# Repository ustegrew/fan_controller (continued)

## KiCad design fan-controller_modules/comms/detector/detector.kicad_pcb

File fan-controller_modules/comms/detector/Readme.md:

# Eval: Detector

KiCad project for an evaluation board providing a fast detector for an AC signal >= 15kHz. This eval board will be realized on a protoype matrix board (pitch 2.54 mm).

Carrier sensitivity can be adjusted.

Detector provides an open collector output. Output is driven low (0V with respect to GND) when no carrier signal is being detected.

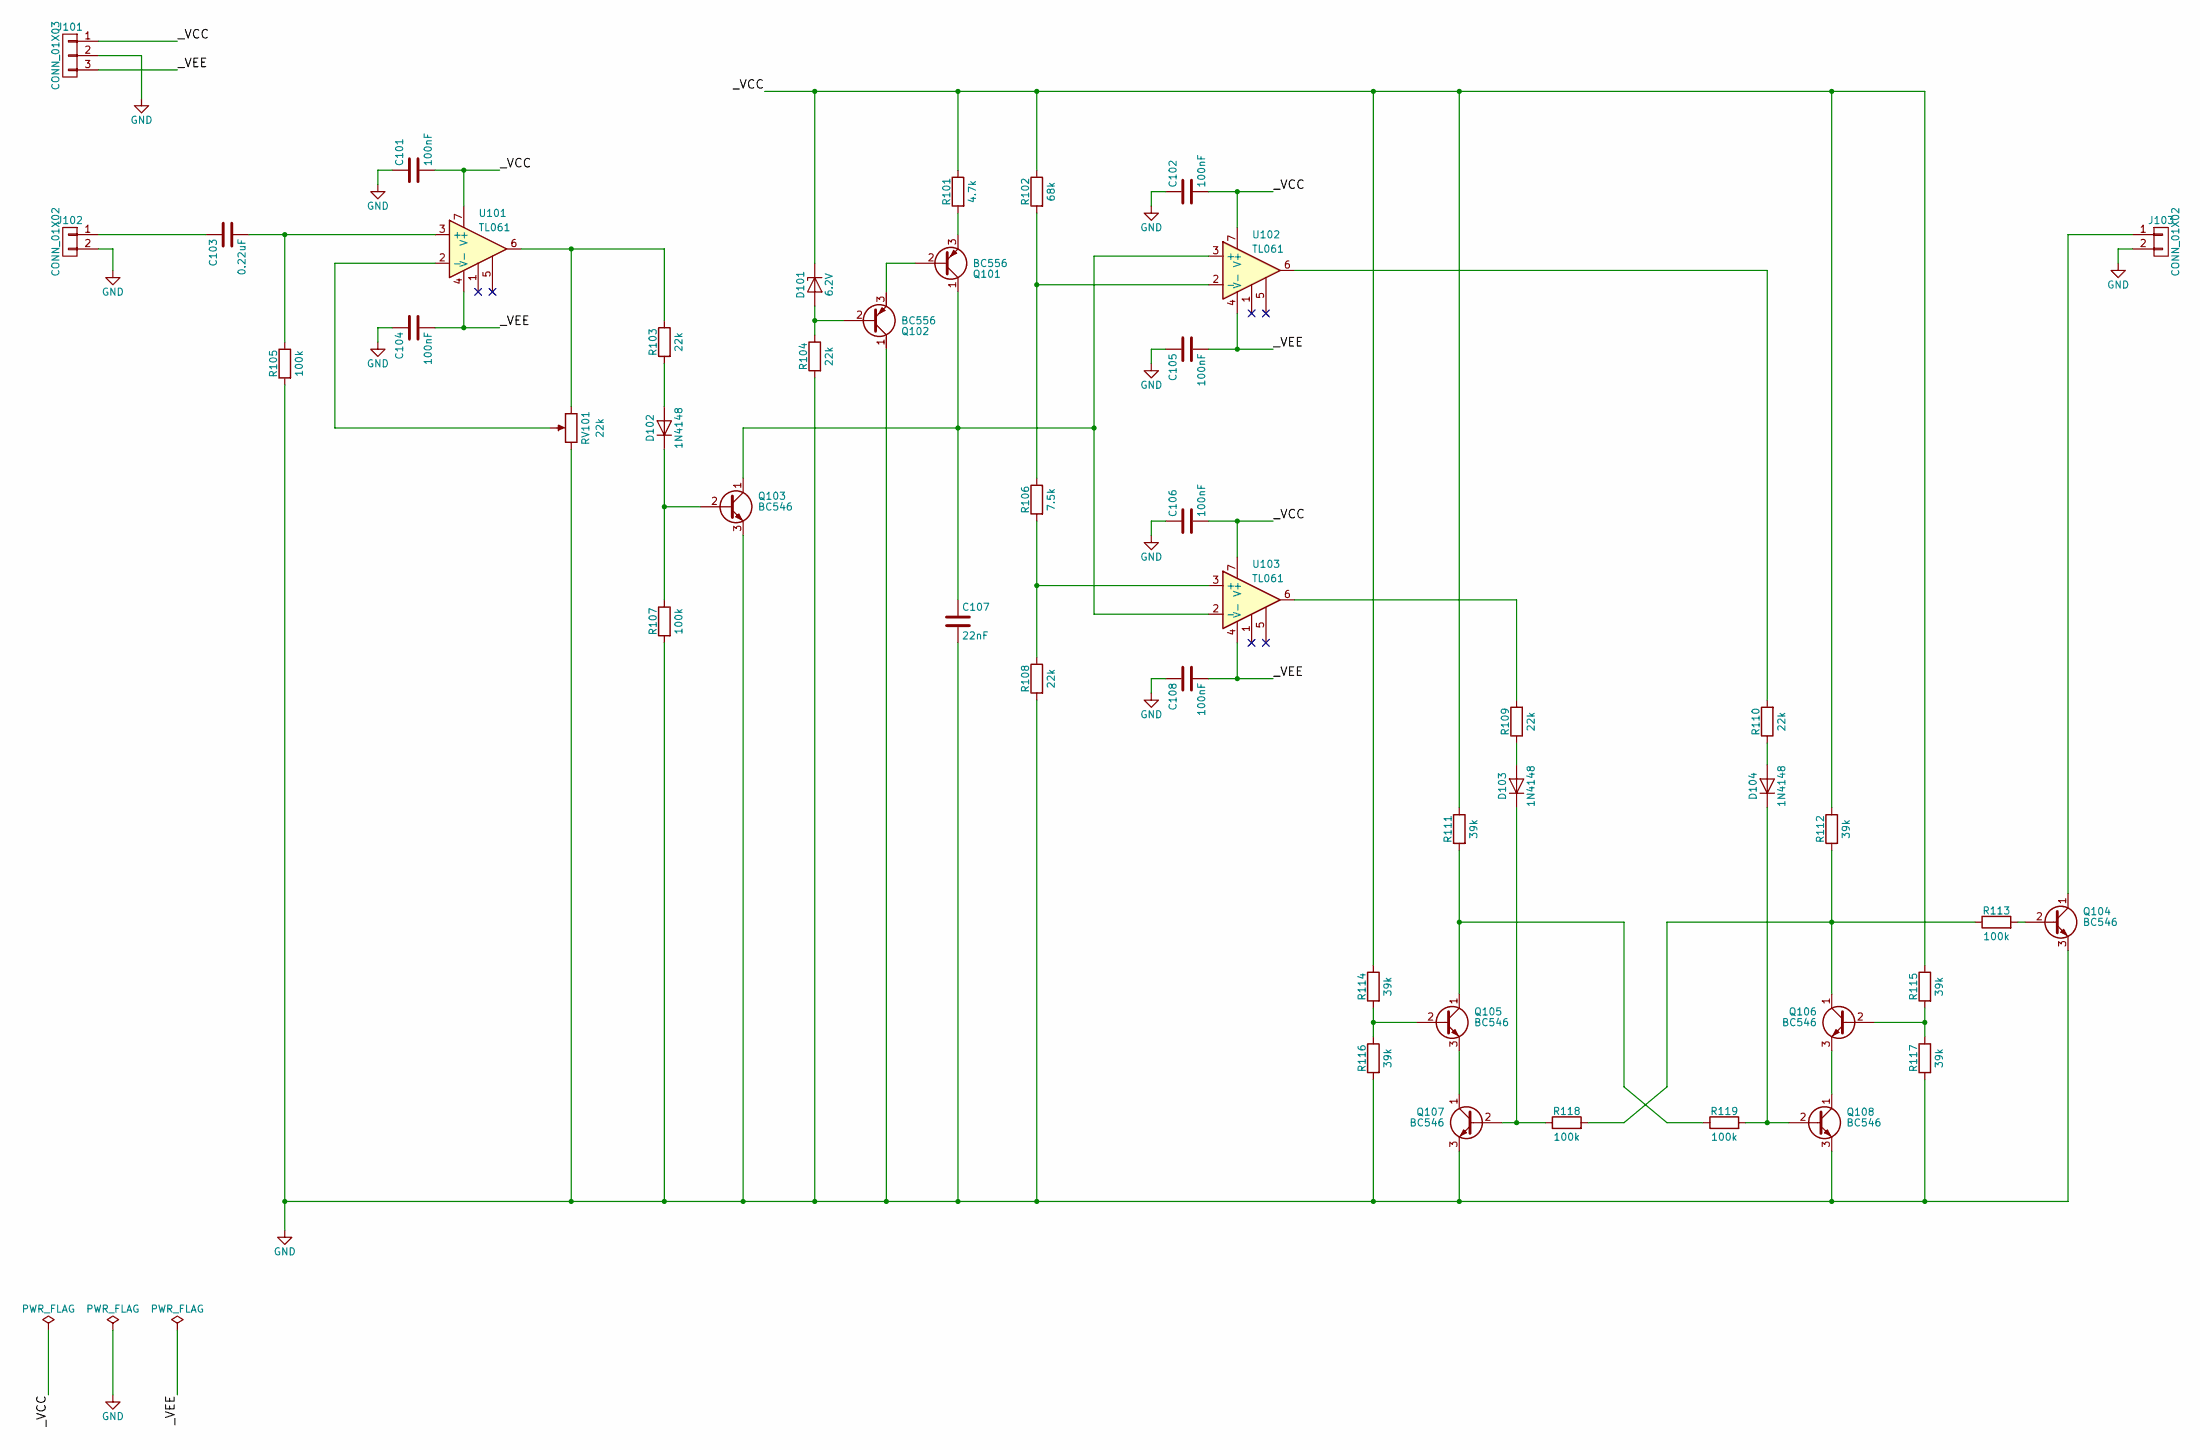
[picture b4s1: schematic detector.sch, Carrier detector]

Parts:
C101, C102: 100nF; C_Rect_L11.0mm_W4.3mm_P10.00mm_MKT
C103: 0.22uF; C_Rect_L7.0mm_W6.0mm_P5.00mm
C104, C105, C106, C108: 100nF; C_Rect_L13.0mm_W6.0mm_P10.00mm_FKS3_FKP3_MKS4
C107: 22nF; C_Rect_L7.2mm_W2.5mm_P5.00mm_FKS2_FKP2_MKS2_MKP2
D101: 6.2V; D_DO-35_SOD27_P7.62mm_Horizontal
D102, D103, D104: 1N4148; D_DO-35_SOD27_P7.62mm_Horizontal
J101: CONN_01X03; Pin_Header_Straight_1x03_Pitch2.54mm
J102, J103: CONN_01X02; Pin_Header_Straight_1x02_Pitch2.54mm
Q101, Q102: BC556; TO-92_Inline_Wide
Q103, Q104, Q105, Q106, Q107, Q108: BC546; TO-92_Inline_Wide
R101: 4.7k; R_Axial_DIN0207_L6.3mm_D2.5mm_P10.16mm_Horizontal
R102: 68k; R_Axial_DIN0414_L11.9mm_D4.5mm_P20.32mm_Horizontal
R103, R104, R108, R109, R110: 22k; R_Axial_DIN0207_L6.3mm_D2.5mm_P10.16mm_Horizontal
R105, R107, R113, R118, R119: 100k; R_Axial_DIN0207_L6.3mm_D2.5mm_P10.16mm_Horizontal
R106: 7.5k; R_Axial_DIN0414_L11.9mm_D4.5mm_P20.32mm_Horizontal
R111, R112, R114, R115, R116, R117: 39k; R_Axial_DIN0411_L9.9mm_D3.6mm_P15.24mm_Horizontal
RV101: 22k; Potentiometer_Trimmer_Piher_PT-10h3.8_Vertical_Px3.8mm_Py5.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
U101, U102, U103: TL061; DIP-8_W7.62mm_LongPads

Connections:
/_VCC: C101.2, C102.2, C106.2, D101.1 (K), J101.1, R101.1, R102.1, R111.1, R112.1, R114.1, R115.1, U101.7 (V+), U102.7 (V+), U103.7 (V+)
/_VEE: C104.2, C105.2, C108.2, J101.3, U101.4 (V-), U102.4 (V-), U103.4 (V-)
GND: C101.1, C102.1, C104.1, C105.1, C106.1, C107.2, C108.1, J101.2, J102.2, J103.2, Q102.1 (C), Q103.3 (E), Q104.3 (E), Q107.3 (E), Q108.3 (E), R104.2, R105.2, R107.2, R108.2, R116.2, R117.2, RV101.3
unnamed: C103.1, J102.1
unnamed: C103.2, R105.1, U101.3 (+)
unnamed: C107.1, Q101.1 (C), Q103.1 (C), U102.3 (+), U103.2 (-)
unnamed: D101.2 (A), Q102.2 (B), R104.1
unnamed: D102.1 (K), Q103.2 (B), R107.1
unnamed: D102.2 (A), R103.2
unnamed: D103.1 (K), Q107.2 (B), R118.1
unnamed: D103.2 (A), R109.1
unnamed: D104.1 (K), Q108.2 (B), R119.2
unnamed: D104.2 (A), R110.1
unnamed: J103.1, Q104.1 (C)
unnamed: Q101.2 (B), Q102.3 (E)
unnamed: Q101.3 (E), R101.2
unnamed: Q104.2 (B), R113.2
unnamed: Q105.1 (C), R111.2, R119.1
unnamed: Q105.2 (B), R114.2, R116.1
unnamed: Q105.3 (E), Q107.1 (C)
unnamed: Q106.1 (C), R112.2, R113.1, R118.2
unnamed: Q106.2 (B), R115.2, R117.1
unnamed: Q106.3 (E), Q108.1 (C)
unnamed: R102.2, R106.1, U102.2 (-)
unnamed: R103.1, RV101.1, U101.6
unnamed: R106.2, R108.1, U103.3 (+)
unnamed: R109.2, U103.6
unnamed: R110.2, U102.6
unnamed: RV101.2, U101.2 (-)

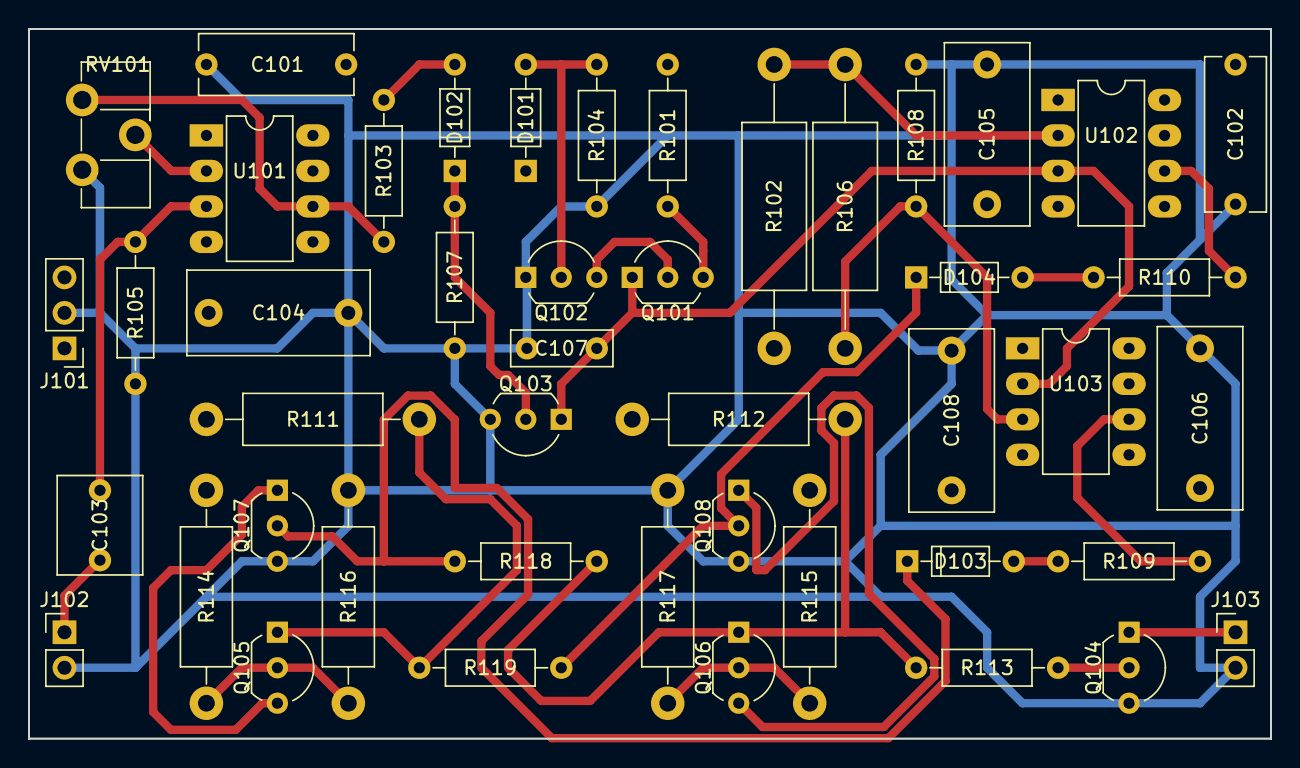
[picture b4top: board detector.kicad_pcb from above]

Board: 4 copper layers, 88.9 x 50.8 mm, 46 parts (0 on the bottom side), 29 nets.

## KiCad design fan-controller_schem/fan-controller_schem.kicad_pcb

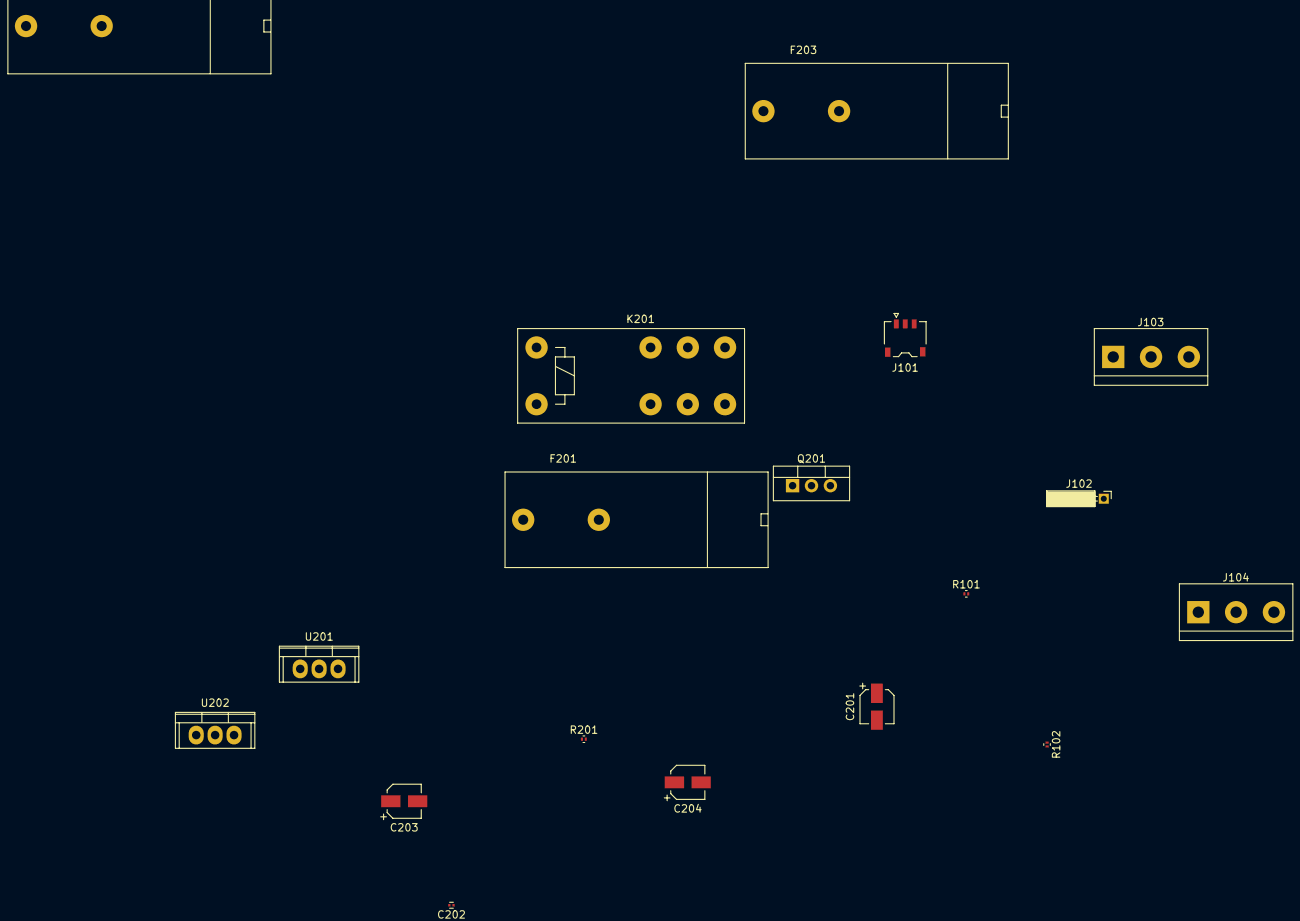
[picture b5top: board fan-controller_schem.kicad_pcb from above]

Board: 2 copper layers, 18 parts (0 on the bottom side), 15 nets, no tracks yet.

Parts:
C201: 100uF/63V; CP_Elec_4x4.5
C202: 0.1 uF; C_0201
C203: 100uF/63V; CP_Elec_4x5.7
C204: 1 uF; CP_Elec_4x5.8
F201: 4AT; Fuseholder5x20_Horizontal_closed_Bulgin_FX0457
F202, F203: 1AT; Fuseholder5x20_Horizontal_closed_Bulgin_FX0457
J101: CONN_01X03_FEMALE; JST_ACH_BM03B-ACHSS_03x1.20mm_Angled
J102: CONN_01X01_FEMALE; Socket_Strip_Angled_1x01_Pitch2.00mm
J103, J104: Screw_Terminal_1x03; bornier3
K201: FINDER-40.52; Relay_DPDT_Finder_40.52
Q201: TIP120; TO-220_Vertical
R101, R102: R; R_0201
R201: 4.7k; R_0201
U201: LM7805; TO-220
U202: 7905; TO-220

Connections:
/PSU/12VAC_IN_1: F202.2, J101.1
/PSU/12VAC_IN_2: C201.2, C202.2, C203.1, C204.1, J101.2, Q201.3, R101.2, R102.1
/PSU/12VAC_IN_3: F203.2, J101.3
/PSU/FAN_ON: J102.1, R201.2
/PSU/L_IN: F201.1, J103.1
/PSU/L_OUT: J104.1, K201.24
/PSU/N_IN: J103.2, K201.11, K201.12
/PSU/N_OUT: J104.2, K201.14
/PSU/PE_IN: J103.3, J104.3
/PSU/VCC_OUT: C202.1, R101.1
/PSU/VEE_OUT: C204.2, R102.2
unnamed: C201.1, K201.A1
unnamed: K201.A2, Q201.2
unnamed: F201.2, K201.21, K201.22
unnamed: Q201.1, R201.1

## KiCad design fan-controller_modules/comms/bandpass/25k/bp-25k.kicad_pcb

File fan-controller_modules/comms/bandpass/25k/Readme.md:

# Eval: Bandpass, 25kHz

KiCad project for an evaluation board providing a 25 kHz bandpass. 

Filter parameters:

* Center frequency: 25kHz
* Passband: -3dB  at 4kHz
* Stopband: -40dB at 15kHz
* Filter type: Butterworth/Bessel

Calculations courtesy [filter wizard](http://www.analog.com/designtools/en/filterwizard) at Analog.com.

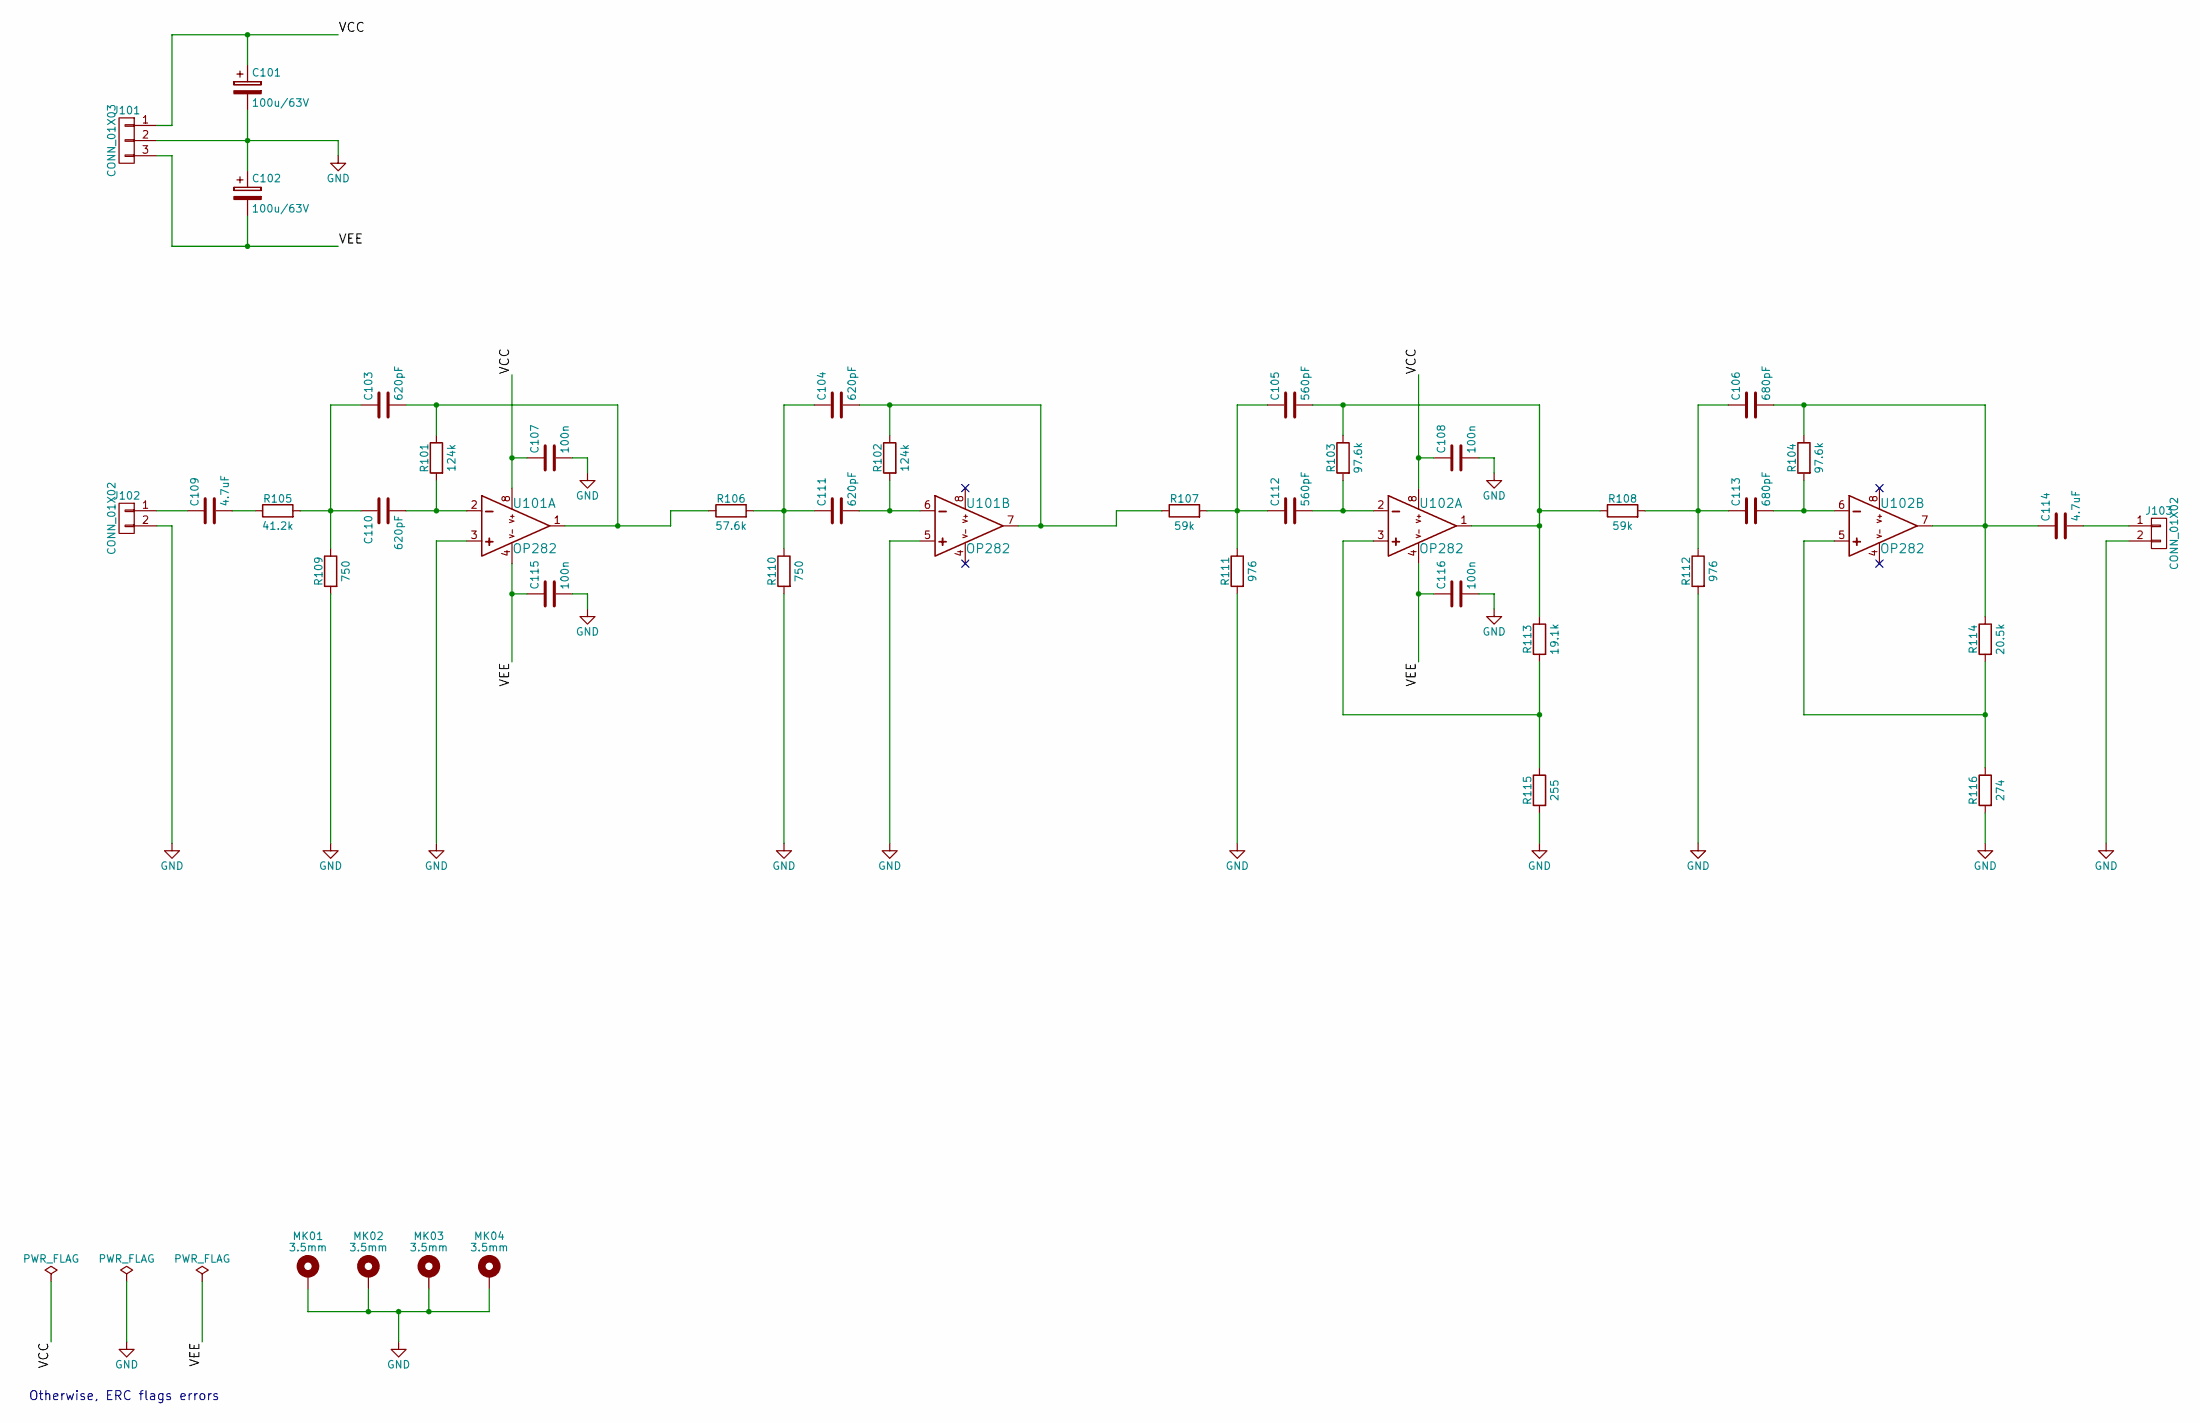
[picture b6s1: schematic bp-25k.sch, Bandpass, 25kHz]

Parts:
C101, C102: 100u/63V; CP_Elec_6.3x7.7
C103, C104, C110, C111: 620pF; C_0603_HandSoldering
C105, C112: 560pF; C_0805_HandSoldering
C106, C113: 680pF; C_0805_HandSoldering
C107, C108, C115, C116: 100n; C_1812_HandSoldering
C109, C114: 4.7uF; C_1206_HandSoldering
J101: CONN_01X03; Pin_Header_Straight_1x03_Pitch2.54mm
J102, J103: CONN_01X02; Pin_Header_Straight_1x02_Pitch2.54mm
MK01, MK02, MK03, MK04: 3.5mm; MountingHole_3.5mm_Pad_Via
R101, R102: 124k; R_0201
R103, R104: 97.6k; R_0201
R105: 41.2k; R_0201
R106: 57.6k; R_0201
R107, R108: 59k; R_0201
R109, R110: 750; R_0201
R111, R112: 976; R_0201
R113: 19.1k; R_0201
R114: 20.5k; R_0201
R115: 255; R_0201
R116: 274; R_0201
U101, U102: OP282; SOIC-8_3.9x4.9mm_Pitch1.27mm

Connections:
/VCC: C101.1, C107.1, C108.1, J101.1, U101.8, U102.8
/VEE: C102.2, C115.1, C116.1, J101.3, U101.4, U102.4
GND: C101.2, C102.1, C107.2, C108.2, C115.2, C116.2, J101.2, J102.2, J103.2, MK01.1, MK02.1, MK03.1, MK04.1, R109.2, R110.2, R111.2, R112.2, R115.2, R116.2, U101.3, U101.5
unnamed: C103.1, C110.1, R105.2, R109.1
unnamed: C103.2, R101.1, R106.1, U101.1
unnamed: C104.1, C111.1, R106.2, R110.1
unnamed: C104.2, R102.1, R107.1, U101.7
unnamed: C105.1, C112.1, R107.2, R111.1
unnamed: C105.2, R103.1, R108.1, R113.1, U102.1
unnamed: C106.1, C113.1, R108.2, R112.1
unnamed: C106.2, C114.1, R104.1, R114.1, U102.7
unnamed: C109.1, J102.1
unnamed: C109.2, R105.1
unnamed: C110.2, R101.2, U101.2
unnamed: C111.2, R102.2, U101.6
unnamed: C112.2, R103.2, U102.2
unnamed: C113.2, R104.2, U102.6
unnamed: C114.2, J103.1
unnamed: R113.2, R115.1, U102.3
unnamed: R114.2, R116.1, U102.5

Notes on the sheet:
Otherwise, ERC flags errors

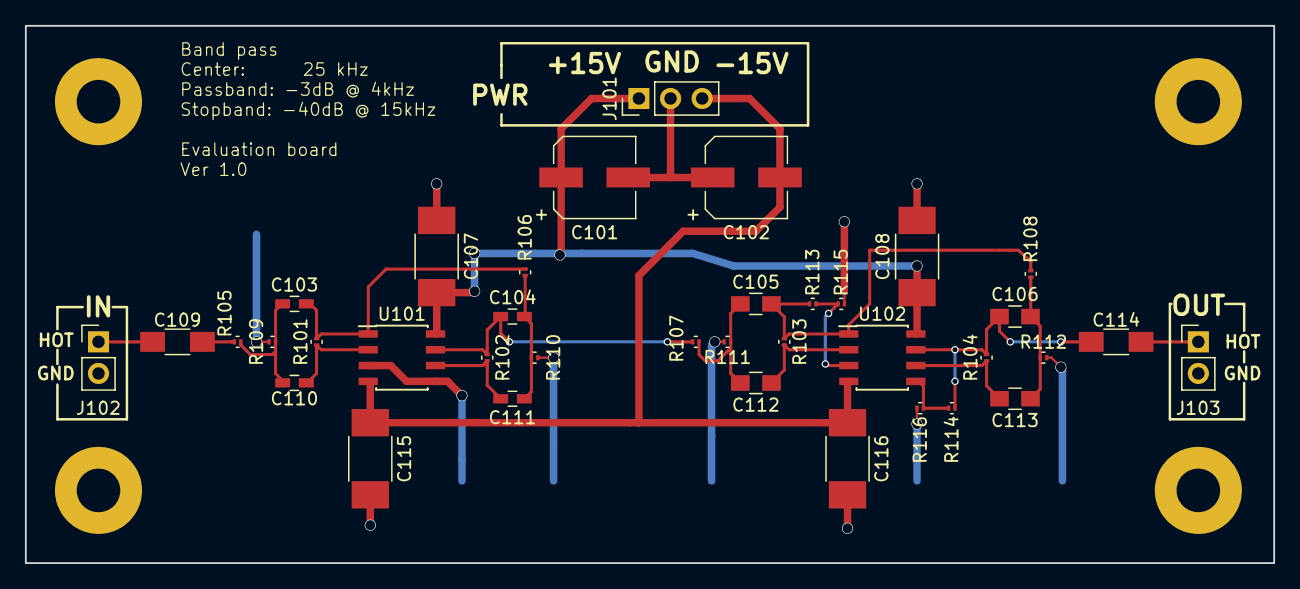
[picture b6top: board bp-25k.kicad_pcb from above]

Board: 2 copper layers, 100.3 x 43.2 mm, 41 parts (0 on the bottom side), 20 nets.

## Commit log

2017-03-19 Initial commit.
2017-03-19 Readme file.
2017-03-19 Fixed link in Readme file.
2017-03-19 Readme fix.
2017-03-19 Readme fixes.
2017-03-22 Writing documentation.
2017-03-22 Revising documentation.
2017-03-22 Pruned sources.
2017-03-22 Removed wiki text content from /doc and put it under git control (https://github.com/ustegrew/fan_controller.wiki.git).
2017-03-22 Recorganizing sources.
2017-03-22 Reorganizing documentation.
2017-03-23 Minor corrections.
2017-03-23 Fixing doc tree problems.
2017-03-23 Fixing source tree problems.
2017-03-31 Developing front panel (ui).
2017-03-31 Revising drawings.
2017-04-02 Revising UI drawing.
2017-04-15 Creating schematics.
2017-04-29 Experimentation phase. Investigations re. frequency characteristics of the TL071 OPAMP.
2017-05-01 Frequency characteristics: Signal transformer.
2017-05-06 Developing 15000Hz filter.
2017-05-08 Annotating schematics: 15000 Hz research filter
2017-07-03 Communication system
2017-07-03 Communication system: Starting oscillator modules.
2017-07-05 Comms, oscillator, 25kHz
2017-07-06 Comms, Oscillator, 25k -> Finalized
2017-07-06 Minor changes.
2017-07-12 Comms: Osc_25k: Finalized Comms: Detector
2017-07-16 Comms: Detector module
2017-08-08 Fixing image.
2017-08-14 Writing documentation. Chose I2C communication protocol for all stakeholders.
2017-08-14 Resized images.
2017-08-17 Reorganized drawings. Writing documentation.
2017-08-18 Modifying surge protection.
2018-01-27 Reorganized file tree. Developing circuitry.
2018-01-27 PDF render
2018-03-04 Developing and integrating comms i/o router.
2018-07-07 Annotation and DRC rule check
2018-07-08 Redesign, signalling.
2018-07-26 Revisions and simplifications
2018-07-28 Diagram cleanup and corrections.
2018-07-28 Replotting.
2018-08-10 Creating BOM (with ordering)
2018-08-27 Controller: Assigned footprints. Designing PCB.
2018-09-09 Upgraded KiCad to v.5 and made plans compatible Implementing PCB
2018-09-11 Implementing PCB.
